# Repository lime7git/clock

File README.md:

# clock
 Digital clock based on ESP32 and WS281b leds.

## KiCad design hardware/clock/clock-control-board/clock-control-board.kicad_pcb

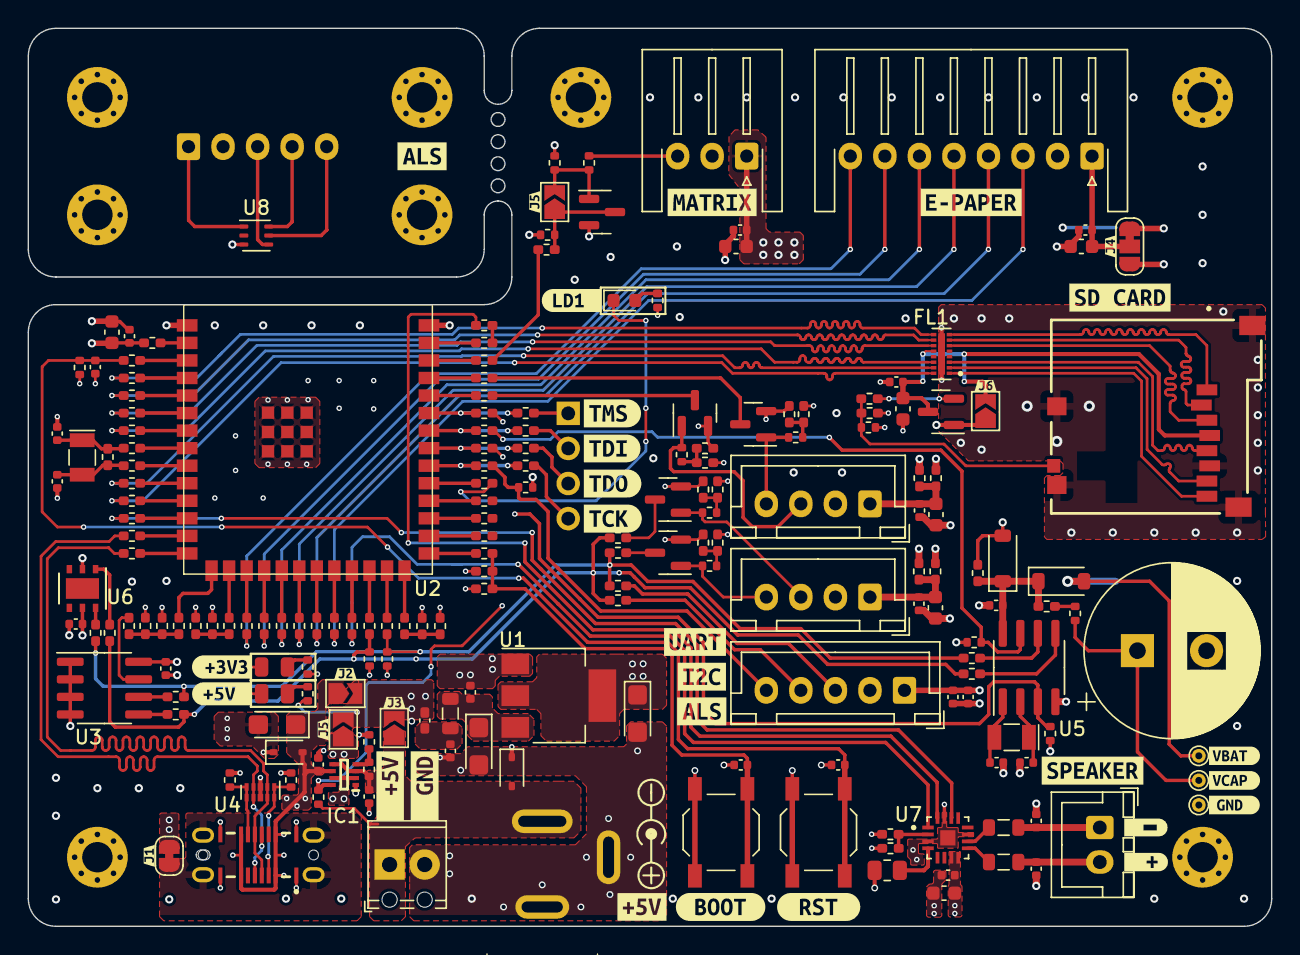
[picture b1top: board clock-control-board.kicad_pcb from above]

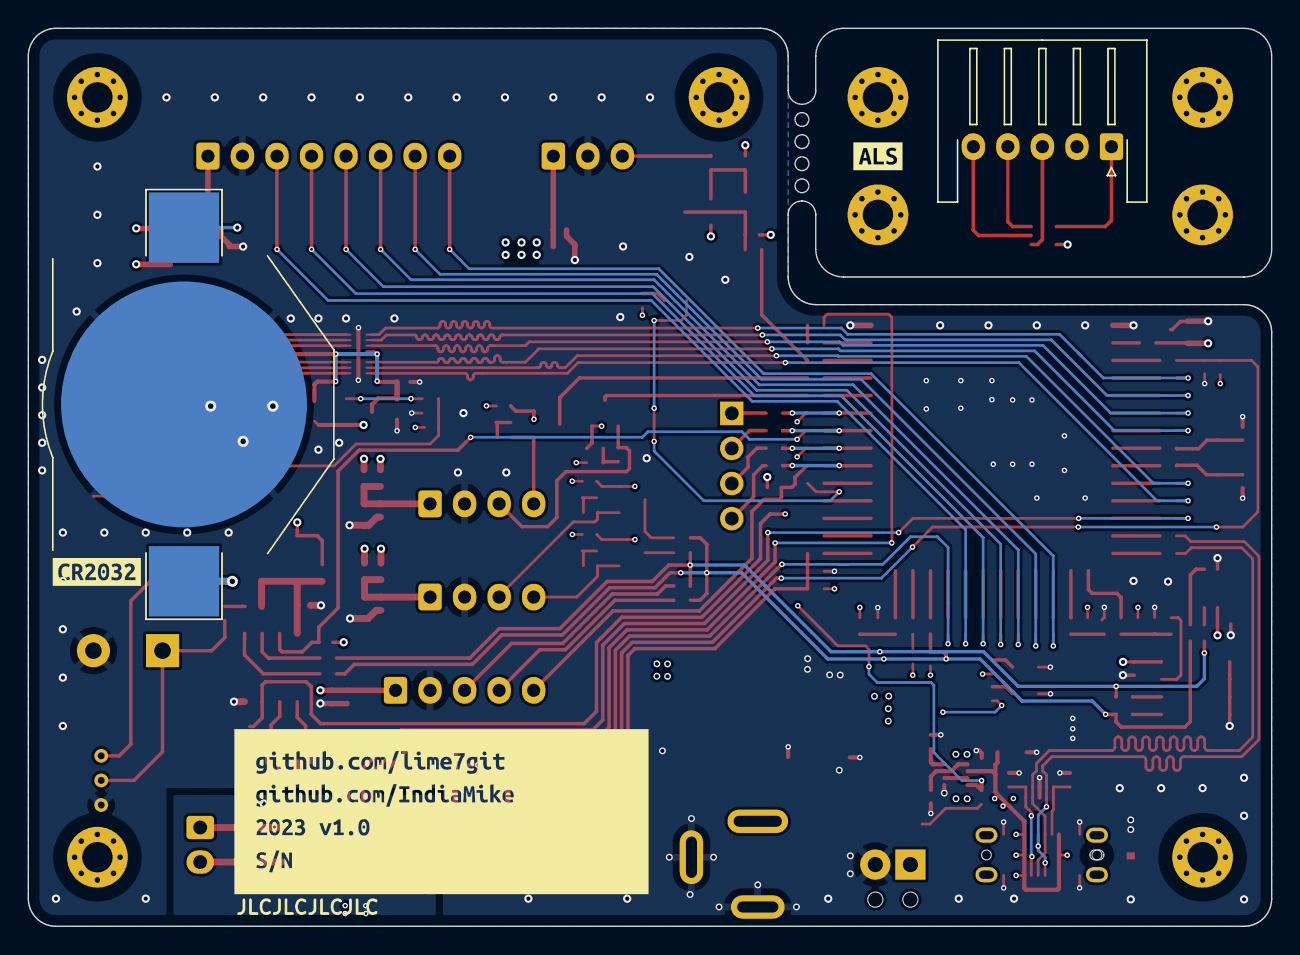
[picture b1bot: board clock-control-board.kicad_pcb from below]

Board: 4 copper layers, 90.0 x 65.0 mm, 239 parts (5 on the bottom side), 142 nets.

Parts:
BT1: Battery_Cell; BatteryHolder_Keystone_3002_1x2032
C1, C2, C11, C23: 1u; C_0402_1005Metric
C3, C4, C36: 10u; CP_EIA-3216-18_Kemet-A
C5, C7, C14, C21, C25, C30, C31: 10uF; C_0603_1608Metric
C6, C8, C12, C13, C15, C19, C20, C22, C24, C26, C29, C32, C33, C34, C35: 100nF; C_0402_1005Metric
C9, C10, C17, C18, C27, C28: 22pF; C_0402_1005Metric
C16: 1F; CP_Radial_D12.5mm_P5.00mm
D1: LED; LED_0603_1608Metric
D2, D5: D_TVS; D_SOD-323
D3, D4: LED; LED_0805_2012Metric
D6, D7: D_Small; D_SOD-123
F1: Fuse; Fuse_0402_1005Metric_Pad0.77x0.64mm_HandSolder
FB1, FB2: FerriteBead_Small; L_0805_2012Metric
FL1: CM1624; FIL_CM1624
H1, H2, H3, H4, H5, H6, H7, H8: MountingHole; MountingHole_2.2mm_M2_Pad_Via
IC1: TPS2116DRLR; SOTFL50P160X60-8N
J1: Jack-DC; PC-GK21
J2: Screw_Terminal_01x02; TerminalBlock_Phoenix_MPT-0,5-2-2.54_1x02_P2.54mm_Horizontal
J3: Conn_01x03; JST_XH_S3B-XH-A-1_1x03_P2.50mm_Horizontal
J4: Conn_01x08; JST_XH_S8B-XH-A-1_1x08_P2.50mm_Horizontal
J5: USB4145-03-0230-C_REVA2; GCT_USB4145-03-0230-C_REVA2
J6: SD_Card; GCT_MEM2051-00-195-00-A_REVD1
J7, J12: Conn_01x04; JST_XH_B4B-XH-A_1x04_P2.50mm_Vertical
J8: Conn_01x05; JST_XH_B5B-XH-A_1x05_P2.50mm_Vertical
J9: Conn_01x05; JST_XH_S5B-XH-A-1_1x05_P2.50mm_Horizontal
J10: Conn_01x02; JST_XH_B2B-XH-A_1x02_P2.50mm_Vertical
J11: JTAG; PinHeader_1x04_P2.54mm_Vertical
JP1, JP2, JP3, JP6, JP7: SolderJumper_2_Open; SolderJumper-2_P1.3mm_Open_TrianglePad1.0x1.5mm
JP4: SolderJumper_3_Bridged12; SolderJumper-3_P1.3mm_Bridged12_RoundedPad1.0x1.5mm
JP5: SolderJumper_2_Bridged; SolderJumper-2_P1.3mm_Bridged_RoundedPad1.0x1.5mm
L1: 100ohm; L_0805_2012Metric
Q2, Q3, Q4, Q5, Q6: NMOS; SOT-23
Q7: PMOS; SOT-23
R1, R4, R5, R19, R37, R38, R42, R44, R51, R70, R72, R83, R98, R101: 10k; R_0402_1005Metric
R2, R100: 2k; R_0402_1005Metric
R3, R105: 1k; R_0402_1005Metric
R6: 220; R_0402_1005Metric
R7, R8, R9, R10, R11, R12, R13, R14, R16, R17, R18, R22, R23, R24, R25, R26, R27, R28, R29, R30, R32, R34, R35, R36, R39, R40, R41, R43, R47, R48, R49, R53, R54, R56, R58, R67, R68, R69, R71, R75, R77, R78, R85, R86, R87, R88, R89, R90, R91, R92, R93, R94, R95, R96, R97, R102, R103, R104, R106: 0 Ohm; R_0402_1005Metric_Pad0.72x0.64mm_HandSolder
R15, R33, R45, R46, R50, R52, R55, R59, R60, R61, R62, R63, R64, R65, R66, R73, R74, R76, R79, R80, R81, R82, R84: DNM; R_0402_1005Metric_Pad0.72x0.64mm_HandSolder
R20, R21, R99: 5.1k; R_0402_1005Metric
R31: 22; R_0402_1005Metric
R57: 680k 1%; R_0805_2012Metric
SW1, SW2: SW_Push; SW_SPST_TL3342
TP1, TP2, TP3: TestPoint; TestPoint_THTPad_D1.0mm_Drill0.5mm
U1: AMS1117-3.3; SOT-223-3_TabPin2
U2: ESP32-S3-WROOM-1-N8R8; ESP32-S3-WROOM-1
U3: M24C64-RMN6TP; SOIC-8_3.9x4.9mm_P1.27mm
U4: RCLAMP0524P-N; USON-10_2.5x1.0mm_P0.5mm
U5: PCF8563T; SOIC-8_3.9x4.9mm_P1.27mm
U6: HDC1080; Texas_PWSON-N6
U7: MAX98357AETE+T; QFN50P300X300X80-17N
U8: LTR-303ALS-01; Lite-On_LTR-303ALS-01
Y1, Y2: 32.768kHz; Crystal_SMD_MicroCrystal_CC7V-T1A-2Pin_3.2x1.5mm
kibuzzard-645AB1F5: G***; kibuzzard-645AB1F5
kibuzzard-645AB20B: G***; kibuzzard-645AB20B
kibuzzard-645AB211: G***; kibuzzard-645AB211
kibuzzard-645BF6F0: G***; kibuzzard-645BF6F0
kibuzzard-645BF6FA: G***; kibuzzard-645BF6FA
kibuzzard-645BF703: G***; kibuzzard-645BF703
kibuzzard-645FAD74: G***; kibuzzard-645FAD74
kibuzzard-6452C2AB: G***; kibuzzard-6452C2AB
kibuzzard-6452C3EF: G***; kibuzzard-6452C3EF
kibuzzard-6456A7AC: G***; kibuzzard-6456A7AC
kibuzzard-6456A7BB: G***; kibuzzard-6456A7BB
kibuzzard-6456A7C9: G***; kibuzzard-6456A7C9
kibuzzard-6456A7D3: G***; kibuzzard-6456A7D3
kibuzzard-6456A84C: G***; kibuzzard-6456A84C
kibuzzard-6456A845: G***; kibuzzard-6456A845
kibuzzard-6456C8A6: G***; kibuzzard-6456C8A6
kibuzzard-6457FC89: G***; kibuzzard-6457FC89
kibuzzard-6457FC92: G***; kibuzzard-6457FC92
kibuzzard-6457FD6A: G***; kibuzzard-6457FD6A
kibuzzard-6457FD19: G***; kibuzzard-6457FD19
kibuzzard-6457FD25: G***; kibuzzard-6457FD25
kibuzzard-6457FDB2: G***; kibuzzard-6457FDB2
kibuzzard-6457FFC6: G***; kibuzzard-6457FFC6
kibuzzard-6457FFFD: G***; kibuzzard-6457FFFD
kibuzzard-645795A5: G***; kibuzzard-645795A5
kibuzzard-645802C2: G***; kibuzzard-645802C2
kibuzzard-646936FC: G***; kibuzzard-646936FC
kibuzzard-6457943A: G***; kibuzzard-6457943A
kibuzzard-6458017F: G***; kibuzzard-6458017F
kibuzzard-6458030B: G***; kibuzzard-6458030B
kibuzzard-6458032B: G***; kibuzzard-6458032B
kibuzzard-6458032F: G***; kibuzzard-6458032F
kibuzzard-64580048: G***; kibuzzard-64580048
kibuzzard-64580318: G***; kibuzzard-64580318
kibuzzard-64580326: G***; kibuzzard-64580326

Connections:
+3.3V: C4.1, C20.1, C23.1, C24.2, C29.2, C30.2, C35.1, D6.2 (A), J8.1, JP4.1 (A), JP6.1 (A), Q2.2 (G), Q3.2 (G), Q4.2 (G), Q5.2 (G), Q6.2 (G), Q7.1 (D), R3.1, R4.2, R19.1, R33.2, R37.2, R38.2, R45.2, R46.2, R50.2, R51.2, R57.1, R58.1, R59.1, R60.1, R61.1, R62.1, R73.2, R74.2, R76.2, R83.2, R98.2, R101.2, R105.1, U1.2 (VO), U3.8 (VCC), U6.5 (VCC)
+5V: C5.1, C6.2, C25.2, C26.1, F1.1, J3.1, JP1.2 (B), JP2.2 (B), JP4.3 (B), JP7.2 (B), R2.1, R5.2, R41.2, R43.2, R49.2, R52.1, R69.2, R71.2, R75.2, U7.7 (VDD), U7.8 (VDD)
/miscellaneous/GAIN: R52.2, R55.1, U7.2 (GAIN_SLOT)
/miscellaneous/LTR_I2C_SCL: J9.3, U8.4 (SCL)
/miscellaneous/LTR_I2C_SDA: J9.4, U8.6 (SDA)
/miscellaneous/LTR_INT_EXT: J9.5, U8.5 (INT)
/miscellaneous/conn_I2C_SCL: J7.4, Q6.1 (D), R44.1
/miscellaneous/conn_I2C_SDA: J7.3, Q5.1 (D), R42.1
/miscellaneous/conn_UART_RX: J12.3, Q3.1 (D), R70.1
/miscellaneous/conn_UART_TX: J12.4, Q4.1 (D), R72.1
/power-section/VOUT: IC1.2 (VOUT_1), IC1.7 (VOUT_2), JP7.1 (A)
/sd-card/CLK: FL1.3 (SDCLK), J6.5 (CLK)
/sd-card/CMD: FL1.6 (SDCMD), J6.2 (CMD)
/sd-card/DAT0: FL1.2 (SDDATA0), J6.7 (DAT0)
/sd-card/DAT1: FL1.1 (SDDATA1), J6.8 (DAT1)
/sd-card/DAT2: FL1.8 (SDDATA2), J6.9 (DAT2)
/sd-card/DAT3: FL1.7 (SDDATA3), J6.1 (CD/DAT3)
/uC-section/CC1: J5.A5 (CC1), R21.1, U4.1 (IO1), U4.10 (NC)
/uC-section/CC2: J5.B5 (CC2), R20.1, U4.5 (IO4), U4.6 (NC)
/uC-section/D+: J5.A6 (DP1), J5.B6 (DP2), R14.1, U4.2 (IO2), U4.9 (NC)
/uC-section/D-: J5.A7 (DN1), J5.B7 (DN2), R13.1, U4.4 (IO3), U4.7 (NC)
/uC-section/EN: C11.2, C13.2, R19.2, R24.1, SW2.2
/uC-section/RXD0: R77.2, U2.36 (RXD0)
/uC-section/TCK: J11.4, R82.2
/uC-section/TDI: J11.2, R80.2
/uC-section/TDO: J11.3, R81.2
/uC-section/TMS: J11.1, R79.2
/uC-section/TXD0: R78.1, U2.37 (TXD0)
/uC-section/uC_IO0: C12.2, R23.2, R59.2, R63.2, SW1.2
/uC-section/uC_IO1: R93.2, R96.2
/uC-section/uC_IO2: R18.2, R86.2, U2.38 (IO2)
/uC-section/uC_IO3: R56.1, R60.2, R64.2, R90.2
/uC-section/uC_IO4: R85.2, U2.4 (IO4)
/uC-section/uC_IO5: R26.2, U2.5 (IO5)
/uC-section/uC_IO6: R27.2, U2.6 (IO6)
/uC-section/uC_IO7: R28.1, U2.7 (IO7)
/uC-section/uC_IO8: R94.2, U2.12 (IO8)
/uC-section/uC_IO9: R87.2, U2.17 (IO9)
/uC-section/uC_IO10: R9.2, U2.18 (IO10)
/uC-section/uC_IO11: R10.2, U2.19 (IO11)
/uC-section/uC_IO12: R11.2, U2.20 (IO12)
/uC-section/uC_IO13: R8.2, U2.21 (IO13)
/uC-section/uC_IO14: R7.2, U2.22 (IO14)
/uC-section/uC_IO15: C10.1, R15.1, R16.1, Y1.1
/uC-section/uC_IO16: C9.1, R15.2, R17.1, Y1.2
/uC-section/uC_IO17: R29.2, U2.10 (IO17)
/uC-section/uC_IO18: R30.1, U2.11 (IO18)
/uC-section/uC_IO21: R95.2, U2.23 (IO21)
/uC-section/uC_IO38: R106.1, U2.31 (IO38)
/uC-section/uC_IO39: R25.2, R82.1, U2.32 (IO39)
/uC-section/uC_IO40: R81.1, R91.2, U2.33 (IO40)
/uC-section/uC_IO41: R80.1, R92.2, U2.34 (IO41)
/uC-section/uC_IO42: R79.1, R97.2, U2.35 (IO42)
/uC-section/uC_IO45: R61.2, R65.2, R88.2
/uC-section/uC_IO46: R62.2, R66.2, R89.2
/uC-section/uC_IO47: R67.2, U2.24 (IO47)
/uC-section/uC_IO48: R68.1, U2.25 (IO48)
BCLK: R93.1, U7.16 (BCLK)
DIN: R95.1, U7.1 (DIN)
EEPROM_WC: R56.2, U3.7 (~WC)
E_PAPER_BUSY: J4.8, R87.1
E_PAPER_CS: J4.5, R11.1
E_PAPER_DC: J4.6, R10.1
E_PAPER_MOSI: J4.3, R7.1
E_PAPER_RST: J4.7, R9.1
E_PAPER_SCK: J4.4, R8.1
GND: BT1.2 (-), C1.1, C2.2, C3.2, C4.2, C5.2, C6.1, C7.1, C8.2, C9.2, C10.2, C11.1, C12.1, C13.1, C14.2, C15.2, C16.2, C17.2, C18.2, C19.1, C20.2, C21.1, C22.2, C23.2, C24.1, C25.1, C26.2, C27.2, C28.2, C29.1, C30.1, C31.1, C32.2, C33.1, C34.1, C35.2, C36.2, D2.1 (A1), D3.1 (K), D4.1 (K), D5.1 (A1), FL1.17 (GND), IC1.1 (GND), J1.2, J2.2, J3.2, J4.2, J5.A1 (GND_A), J5.A12 (GND_A), J5.B1 (GND_B), J5.B12 (GND_B), J6.3 (VSS), J6.6 (VSS), J6.12 (SHELL1), J6.13 (SHELL2), J7.2, J8.2, J12.2, JP5.1 (A), R20.2, R21.2, R55.2, R63.1, R64.1, R65.1, R66.1, R84.1, R100.2, SW1.1, SW2.1, TP3.1, U1.1 (GND), U2.1 (GND), U2.40 (GND), U2.41 (EPAD), U3.1 (E0), U3.2 (E1), U3.3 (E2), U3.4 (VSS), U4.3 (G), U4.8 (G), U5.4 (VSS), U6.2 (GND), U7.3 (GND), U7.11 (GND), U7.15 (GND), U7.17 (EP)
GND_LTR: J9.2, U8.3 (GND)
I2C_SCL: R34.2, R36.1, R40.1, R47.2, R53.1, R68.2, R98.1
I2C_SDA: R22.2, R35.2, R39.2, R48.2, R54.1, R67.1, R101.1
LED_MATRIX_DATA: JP3.1 (A), Q2.3 (S), R4.1, R18.1
LRCLK: R94.1, U7.14 (LRCLK)
LTR_INT: J8.5, R25.1, R51.1
unnamed: BT1.1 (+), D7.2 (A), TP2.1
unnamed: C1.2, F1.2, L1.1
unnamed: C16.1, R31.1, TP1.1
unnamed: D1.2 (A), R105.2
unnamed: D1.1 (K), R106.2
unnamed: D3.2 (A), R2.2
unnamed: D4.2 (A), R3.2
unnamed: C19.2, D6.1 (K), D7.1 (K), R32.2, R33.1, U5.8 (VDD)
unnamed: IC1.4 (PR1), R99.2, R100.1
unnamed: J3.3, R6.2
unnamed: J6.10 (CARD_DETECT), R12.2, R83.1, R84.2
unnamed: C21.2, C22.1, J7.1, R49.1, R50.1
unnamed: J8.3, R53.2
unnamed: J8.4, R54.2
unnamed: C27.1, FB2.2, J10.1
unnamed: C28.1, FB1.1, J10.2
unnamed: C31.2, C32.1, J12.1, R75.1, R76.1
unnamed: JP3.2 (B), Q2.1 (D), R5.1, R6.1
unnamed: J5.S1 (SHIELD), J5.S2 (SHIELD), J5.S3 (SHIELD), J5.S4 (SHIELD), JP5.2 (B)
unnamed: Q5.3 (S), R39.1
unnamed: Q6.3 (S), R40.2
unnamed: Q7.2 (G), R12.1
unnamed: R31.2, R32.1
unnamed: R41.1, R42.2, R45.1
unnamed: R43.1, R44.2, R46.1
unnamed: R69.1, R70.2, R73.1
unnamed: R71.1, R72.2, R74.1
unnamed: C2.1, C3.1, L1.2, U1.3 (VI)
unnamed: R58.2, U2.2 (3V3)
unnamed: R24.2, U2.3 (EN)
unnamed: R23.1, U2.27 (IO0)
unnamed: R96.1, U2.39 (IO1)
unnamed: R90.1, U2.15 (IO3)
unnamed: R16.2, U2.8 (IO15)
unnamed: R17.2, U2.9 (IO16)
unnamed: R13.2, U2.13 (IO19)
unnamed: R14.2, U2.14 (IO20)
unnamed: R102.1, U2.28 (IO35)
unnamed: R103.1, U2.29 (IO36)
unnamed: R104.1, U2.30 (IO37)
unnamed: R88.1, U2.26 (IO45)
unnamed: R89.1, U2.16 (IO46)
unnamed: R36.2, U3.6 (SCL)
unnamed: R22.1, U3.5 (SDA)
unnamed: C17.1, U5.1 (OSCI), Y2.2
unnamed: C18.1, U5.2 (OSCO), Y2.1
unnamed: R34.1, U5.6 (SCL)
unnamed: R35.1, U5.5 (SDA)
unnamed: R47.1, U6.6 (SCL)
unnamed: R48.1, U6.1 (SDA)
unnamed: FB2.1, U7.10 (OUTN)
unnamed: FB1.2, U7.9 (OUTP)
unnamed: R57.2, U7.4 (SD_MODE)
POWER_STATUS: IC1.8 (ST), R1.1, R97.1
RTC_CLK_OUT: R37.1, R92.1, U5.7 (CLKO)
RTC_INT: R38.1, R91.1, U5.3 (~INT)
SD_CLK: FL1.14 (CLK), R28.2
SD_CMD: FL1.11 (CMD), R27.1
SD_DATA0: FL1.15 (DATA0), R29.1
SD_DATA1: FL1.16 (DATA1), R30.2
SD_DATA2: FL1.9 (DATA2), R85.1
SD_DATA3: FL1.10 (DATA3), R26.1
UART_RX: Q3.3 (S), R77.1
UART_TX: Q4.3 (S), R78.2
VBUS: C33.2, C36.1, D5.2 (A2), IC1.6 (VIN2), J5.A4 (VBUS_A), J5.A9 (VBUS_A), J5.B4 (VBUS_B), J5.B9 (VBUS_B), JP1.1 (A)
VCC: C34.2, D2.2 (A2), IC1.3 (VIN1), IC1.5 (MODE), J1.1, J2.1, JP2.1 (A), R1.2, R99.1
VCC_E_PAPER_DISPLAY: C7.2, C8.1, J4.1, JP4.2 (C)
VCC_LTR: J9.1, U8.1 (VDD)
VCC_SD_CARD: C14.1, C15.1, FL1.12 (VCC), J6.4 (VDD), JP6.2 (B), Q7.3 (S)

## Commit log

2023-08-19 hardware version 1.0
2023-12-27 blink initial application
2024-01-01 added python script for creating .c and .h file templates
2024-01-27 Added led component/led task/log task
2024-01-27 added iot button component task for boot button usage
2024-01-27 suspending and resuming led task from button callbacks
2024-01-28 Squashed commit of the following:
    suspending and resuming led task from button callbacks
    added iot button component task for boot button usage
